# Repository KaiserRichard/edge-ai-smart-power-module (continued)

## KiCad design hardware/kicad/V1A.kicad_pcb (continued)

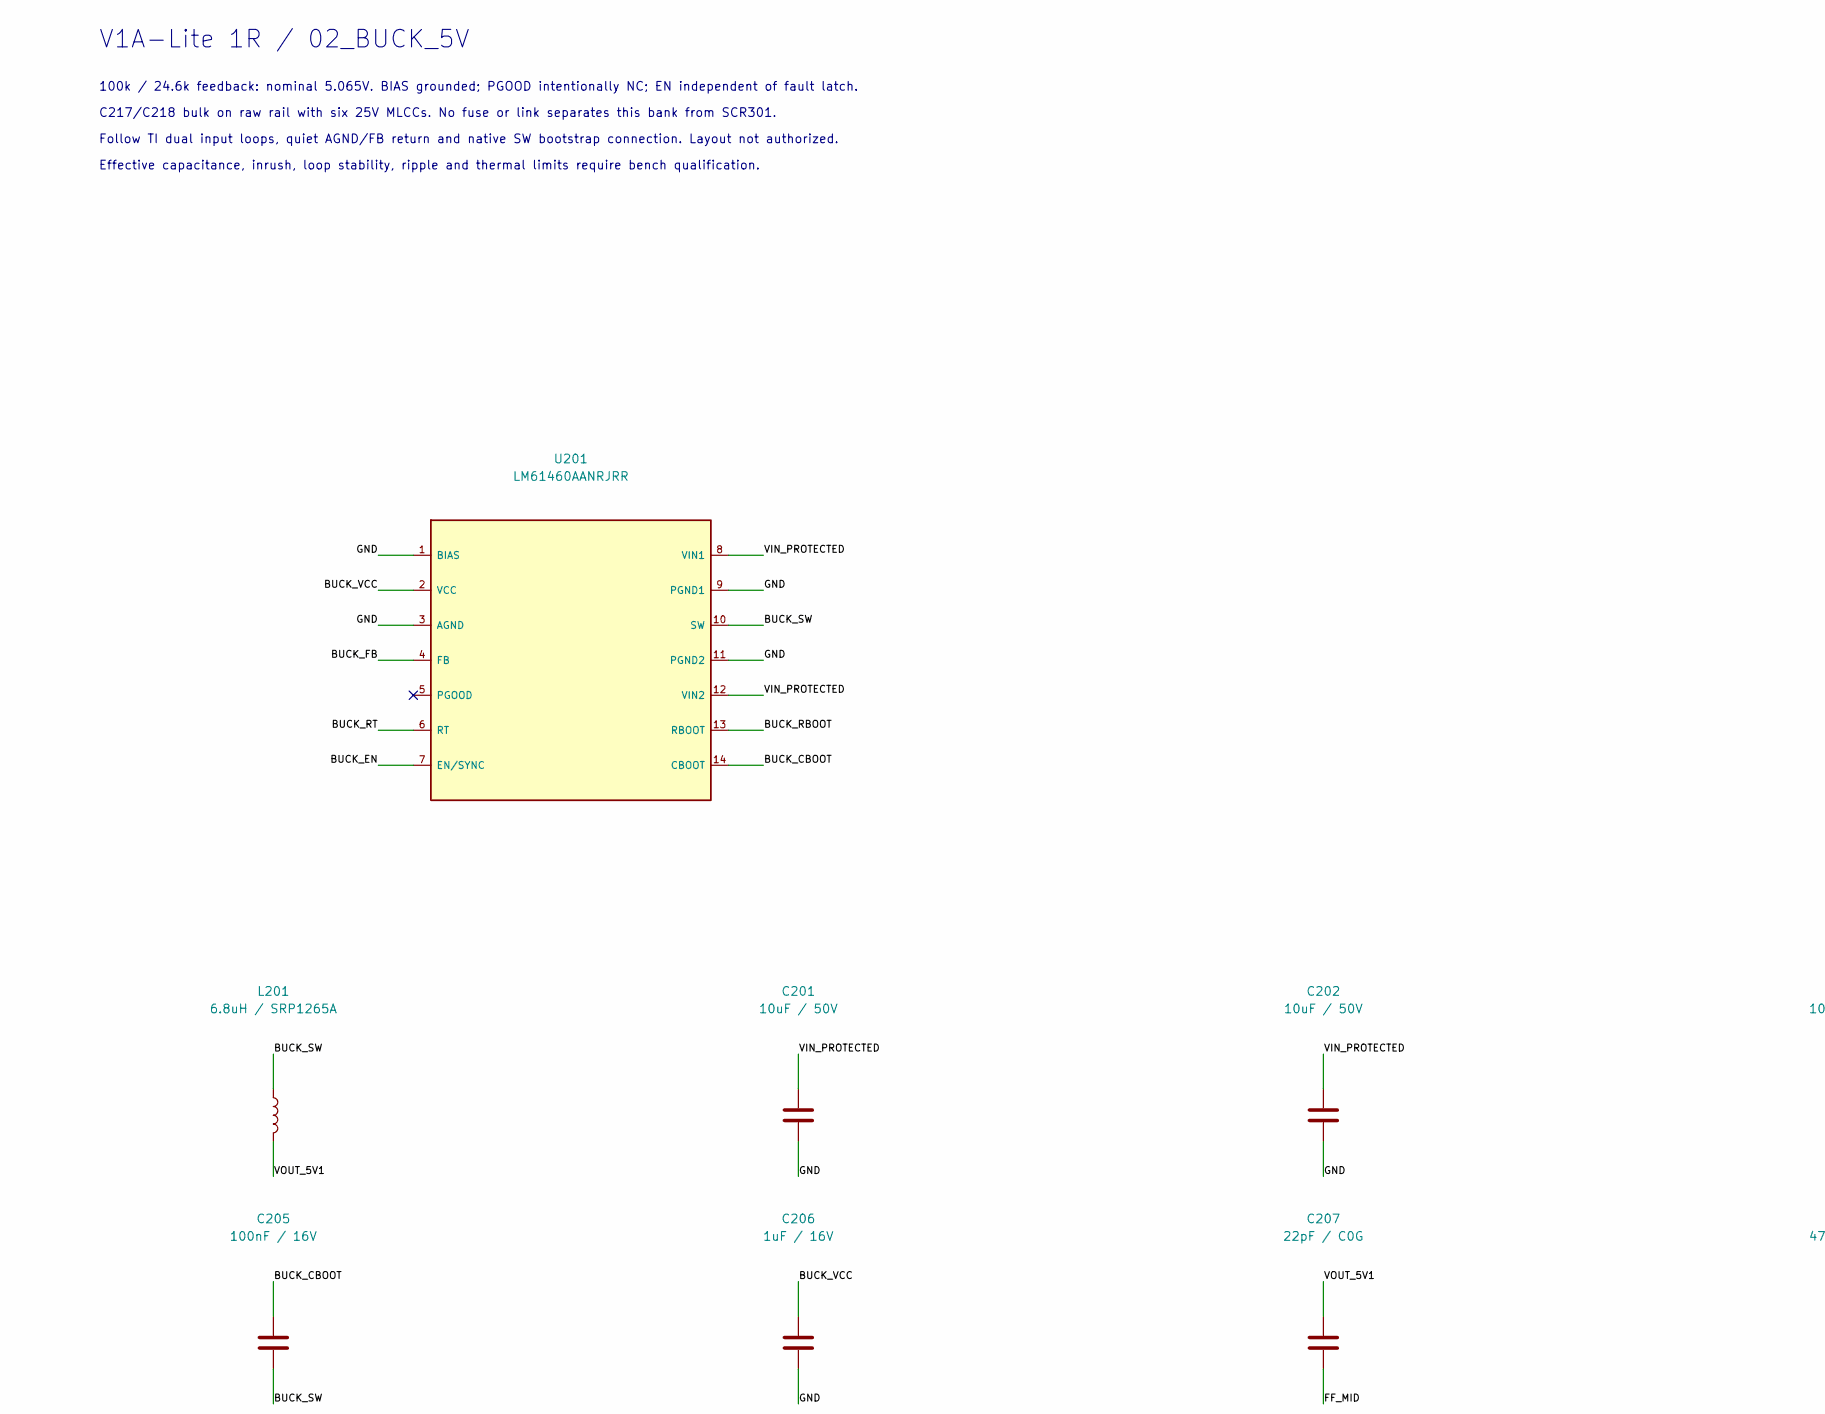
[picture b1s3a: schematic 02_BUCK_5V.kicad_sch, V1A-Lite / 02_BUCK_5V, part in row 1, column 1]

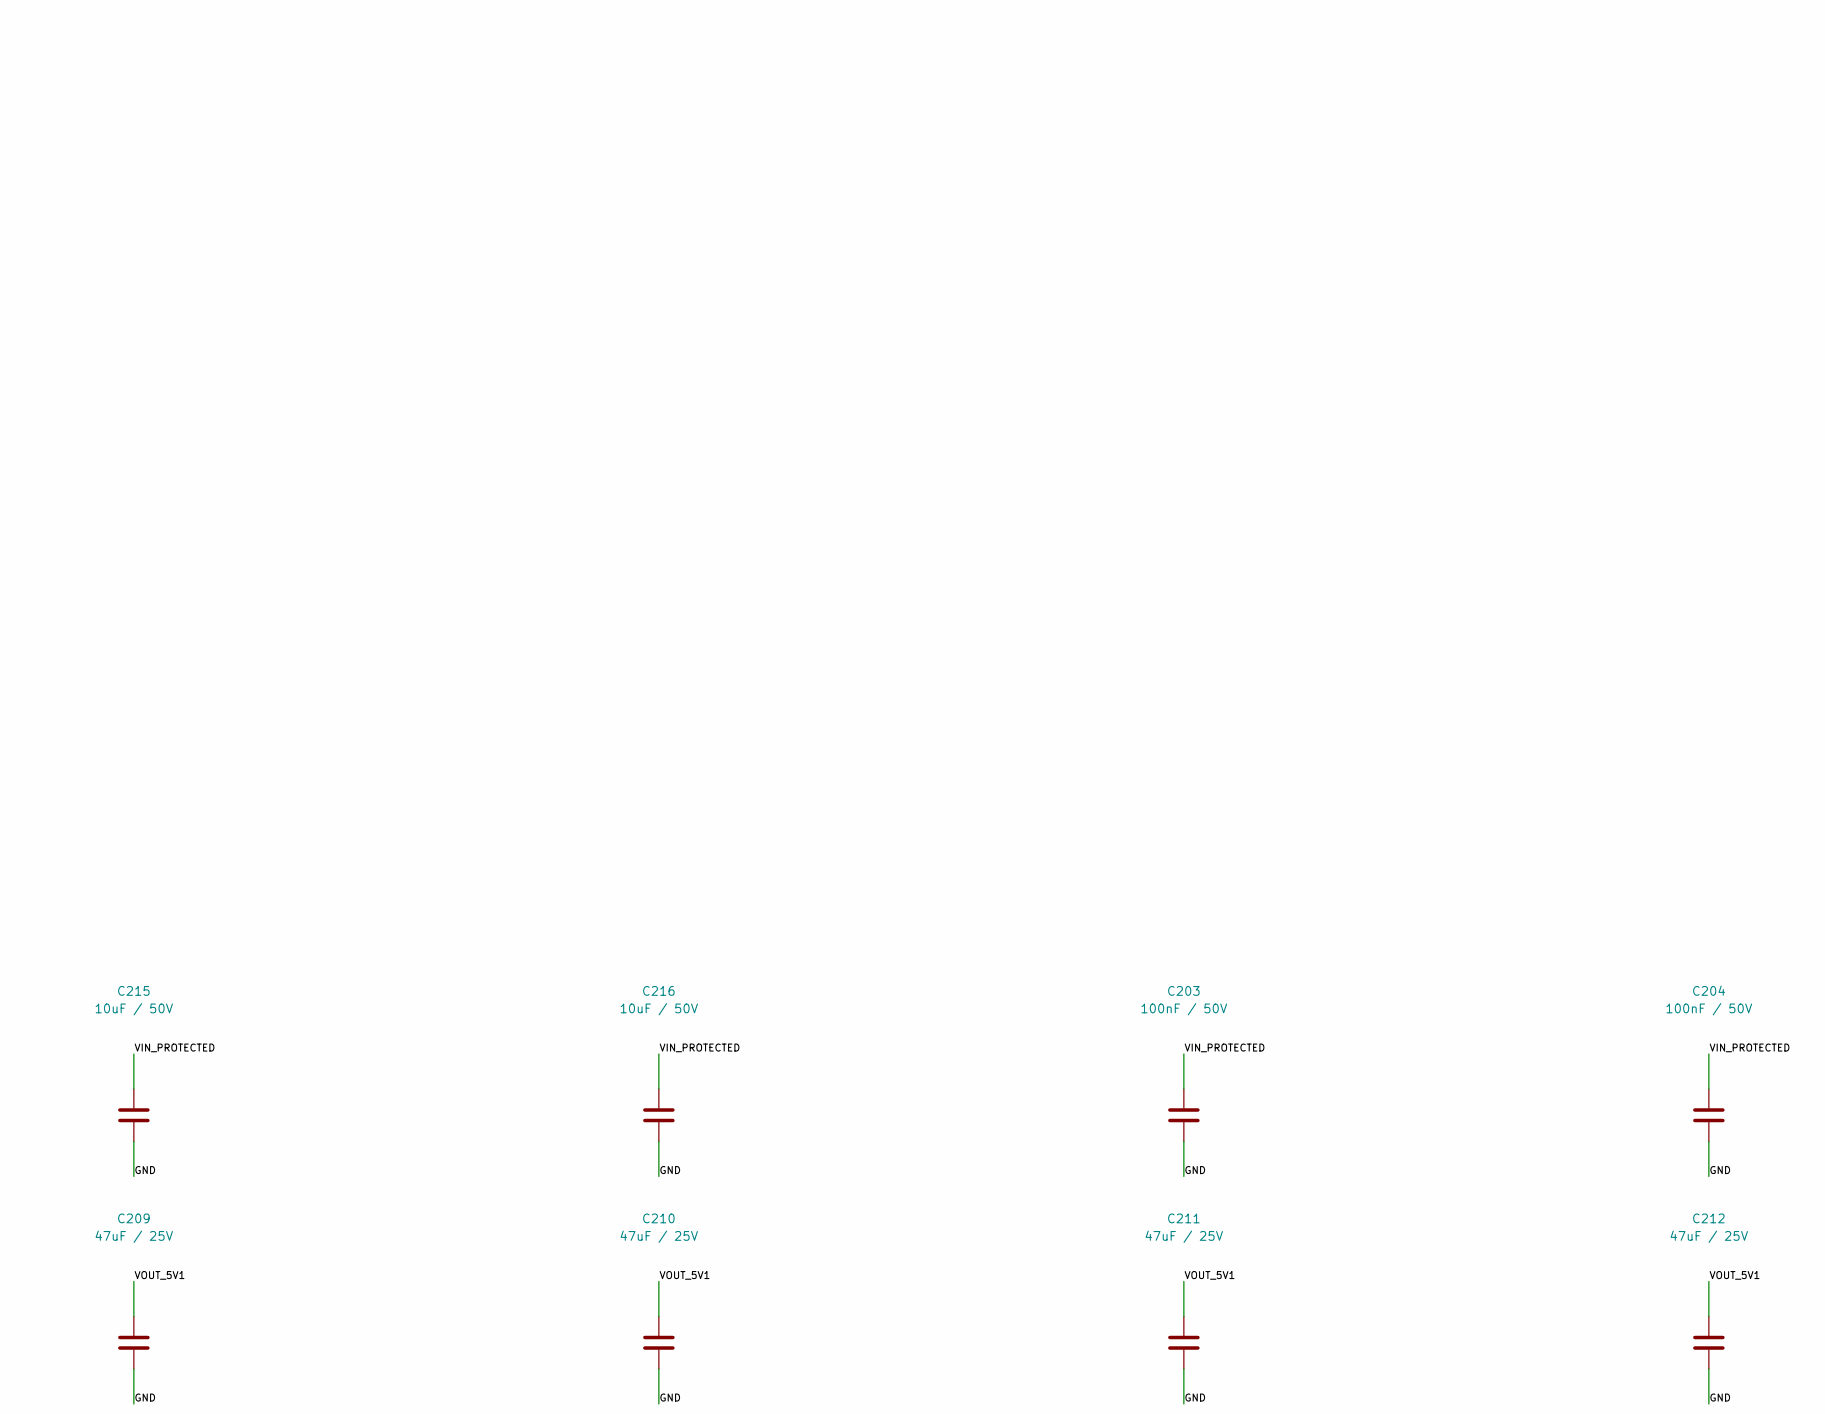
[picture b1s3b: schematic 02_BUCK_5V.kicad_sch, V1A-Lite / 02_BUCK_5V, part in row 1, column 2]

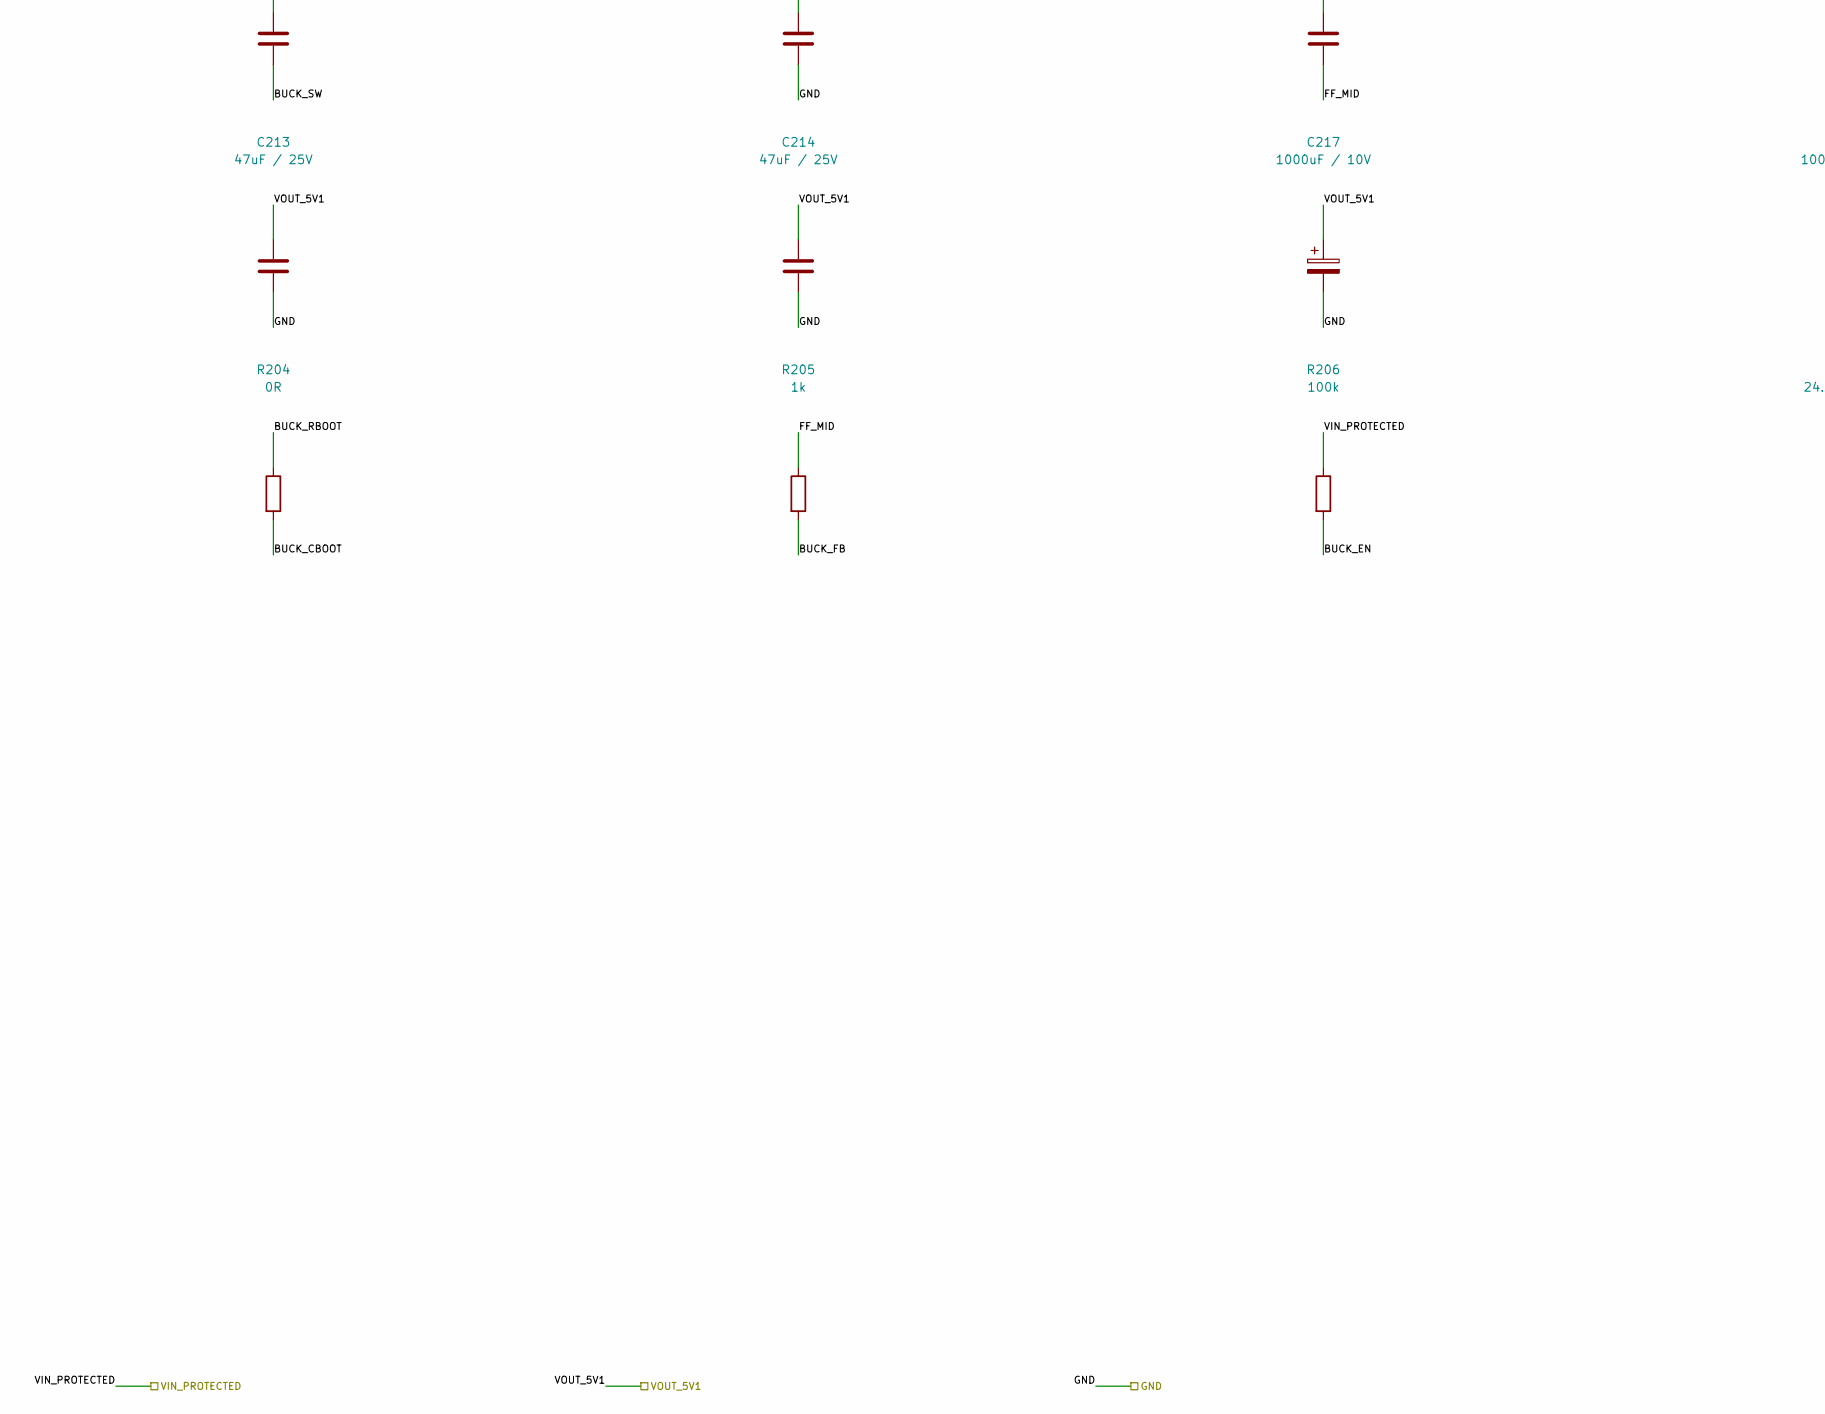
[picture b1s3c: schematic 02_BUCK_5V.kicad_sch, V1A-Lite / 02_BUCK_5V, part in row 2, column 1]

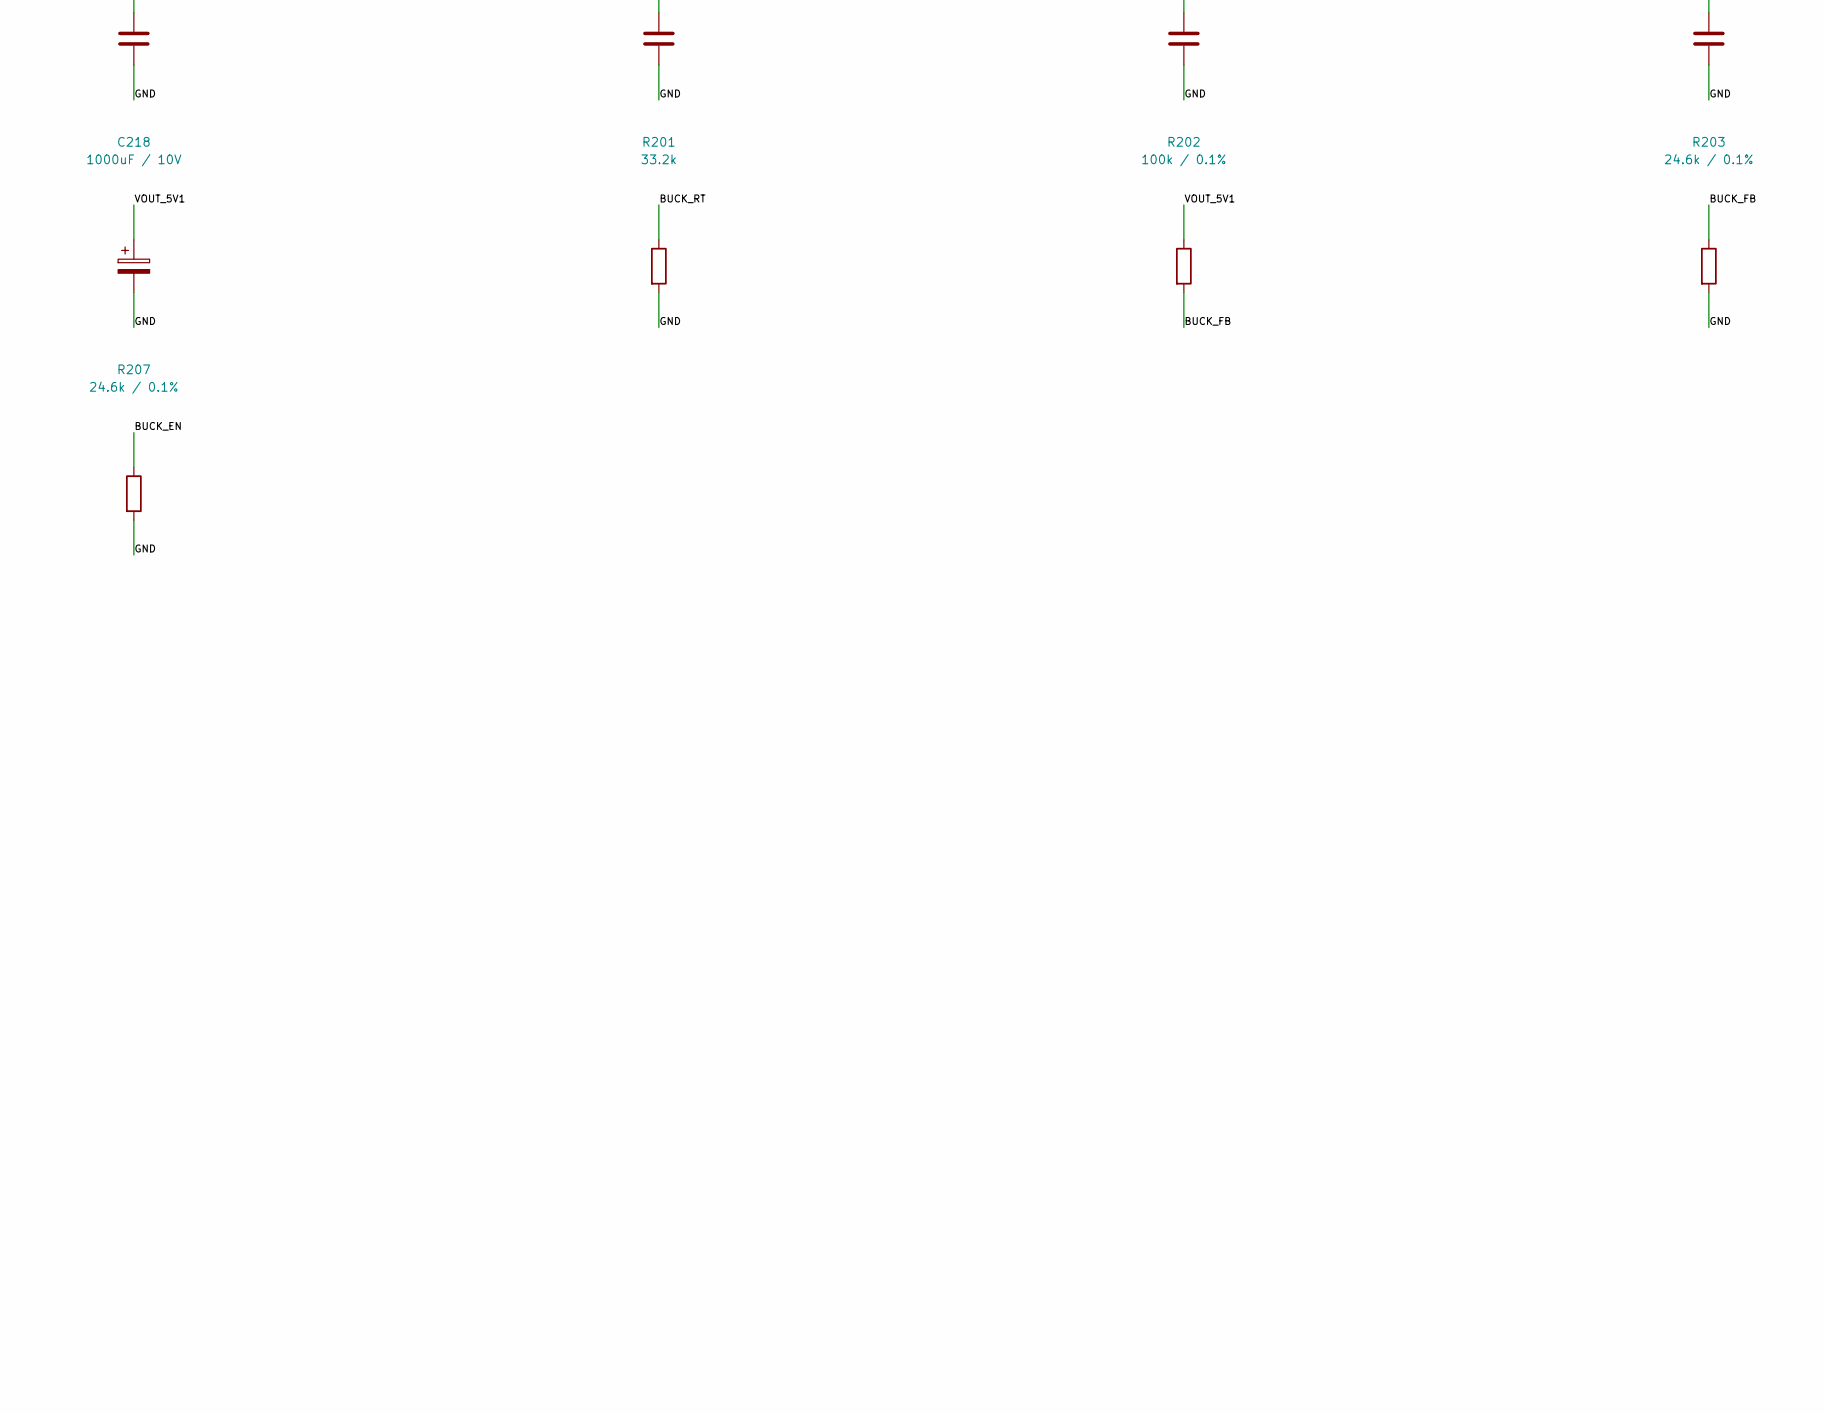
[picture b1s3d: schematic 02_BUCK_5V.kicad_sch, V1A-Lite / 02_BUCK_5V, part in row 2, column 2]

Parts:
C201, C202, C215, C216: 10uF / 50V; C_1210_3225Metric; MPN GRM32ER71H106KA12L; LCSC C77102
C203, C204: 100nF / 50V; C_0603_1608Metric; MPN GRM188R71H104KA93D; LCSC C77055
C205: 100nF / 16V; C_0603_1608Metric; MPN GRM188R71C104KA01D; LCSC C45000
C206: 1uF / 16V; C_0805_2012Metric; MPN GRM21BR71C105KA01L; LCSC C77079
C207: 22pF / C0G; C_0402_1005Metric; MPN C0402C220J4GACTU; LCSC C2168192
C209, C210, C211, C212, C213, C214: 47uF / 25V; C_1206_3216Metric; MPN GRM31CR61E476ME44L; LCSC C403725
C217, C218: 1000uF / 10V; CP_Radial_D10.0mm_P5.00mm; MPN EEUFR1A102; LCSC C407868
L201: 6.8uH / SRP1265A; Bourns_SRP1265A; MPN SRP1265A-6R8M; LCSC C2041326
R201: 33.2k; R_0603_1608Metric; MPN TNPW060333K2BEEA; LCSC C2075328
R202: 100k / 0.1%; R_0603_1608Metric; MPN TNPW0603100KBEEA; LCSC C844888
R203, R207: 24.6k / 0.1%; R_0603_1608Metric; MPN RT0603BRD0724K6L; LCSC C861250
R204: 0R; R_0603_1608Metric; MPN 0603WAF100JT5E; LCSC C22859
R205: 1k; R_0603_1608Metric; MPN 0603WAF1001T5E; LCSC C21190
R206: 100k; R_0603_1608Metric; MPN 0603WAF1003T5E; LCSC C25803
U201: LM61460AANRJRR; TI_RJR0014A_LM61460; MPN LM61460AANRJRR; LCSC C2864505

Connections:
/02_BUCK_5V/BUCK_CBOOT: C205.1, R204.2, U201.14 (CBOOT)
/02_BUCK_5V/BUCK_EN: R206.2, R207.1, U201.7 (EN/SYNC)
/02_BUCK_5V/BUCK_FB: R202.2, R203.1, R205.2, U201.4 (FB)
/02_BUCK_5V/BUCK_RBOOT: R204.1, U201.13 (RBOOT)
/02_BUCK_5V/BUCK_RT: R201.1, U201.6 (RT)
/02_BUCK_5V/BUCK_SW: C205.2, L201.1, U201.10 (SW)
/02_BUCK_5V/BUCK_VCC: C206.1, U201.2 (VCC)
/02_BUCK_5V/FF_MID: C207.2, R205.1
/GND: C201.2, C202.2, C203.2, C204.2, C206.2, C209.2, C210.2, C211.2, C212.2, C213.2, C214.2, C215.2, C216.2, C217.2, C218.2, R201.2, R203.2, R207.2, U201.1 (BIAS), U201.3 (AGND), U201.9 (PGND1), U201.11 (PGND2); also elsewhere on the board
/VIN_PROTECTED: C201.1, C202.1, C203.1, C204.1, C215.1, C216.1, R206.1, U201.8 (VIN1), U201.12 (VIN2); also elsewhere on the board
/VOUT_5V1: C207.1, C209.1, C210.1, C211.1, C212.1, C213.1, C214.1, C217.1, C218.1, L201.2, R202.1; also elsewhere on the board

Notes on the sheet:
V1A-Lite 1R / 02_BUCK_5V
100k / 24.6k feedback: nominal 5.065V. BIAS grounded; PGOOD intentionally NC; EN independent of fault latch.
C217/C218 bulk on raw rail with six 25V MLCCs. No fuse or link separates this bank from SCR301.
Follow TI dual input loops, quiet AGND/FB return and native SW bootstrap connection. Layout not authorized.
Effective capacitance, inrush, loop stability, ripple and thermal limits require bench qualification.

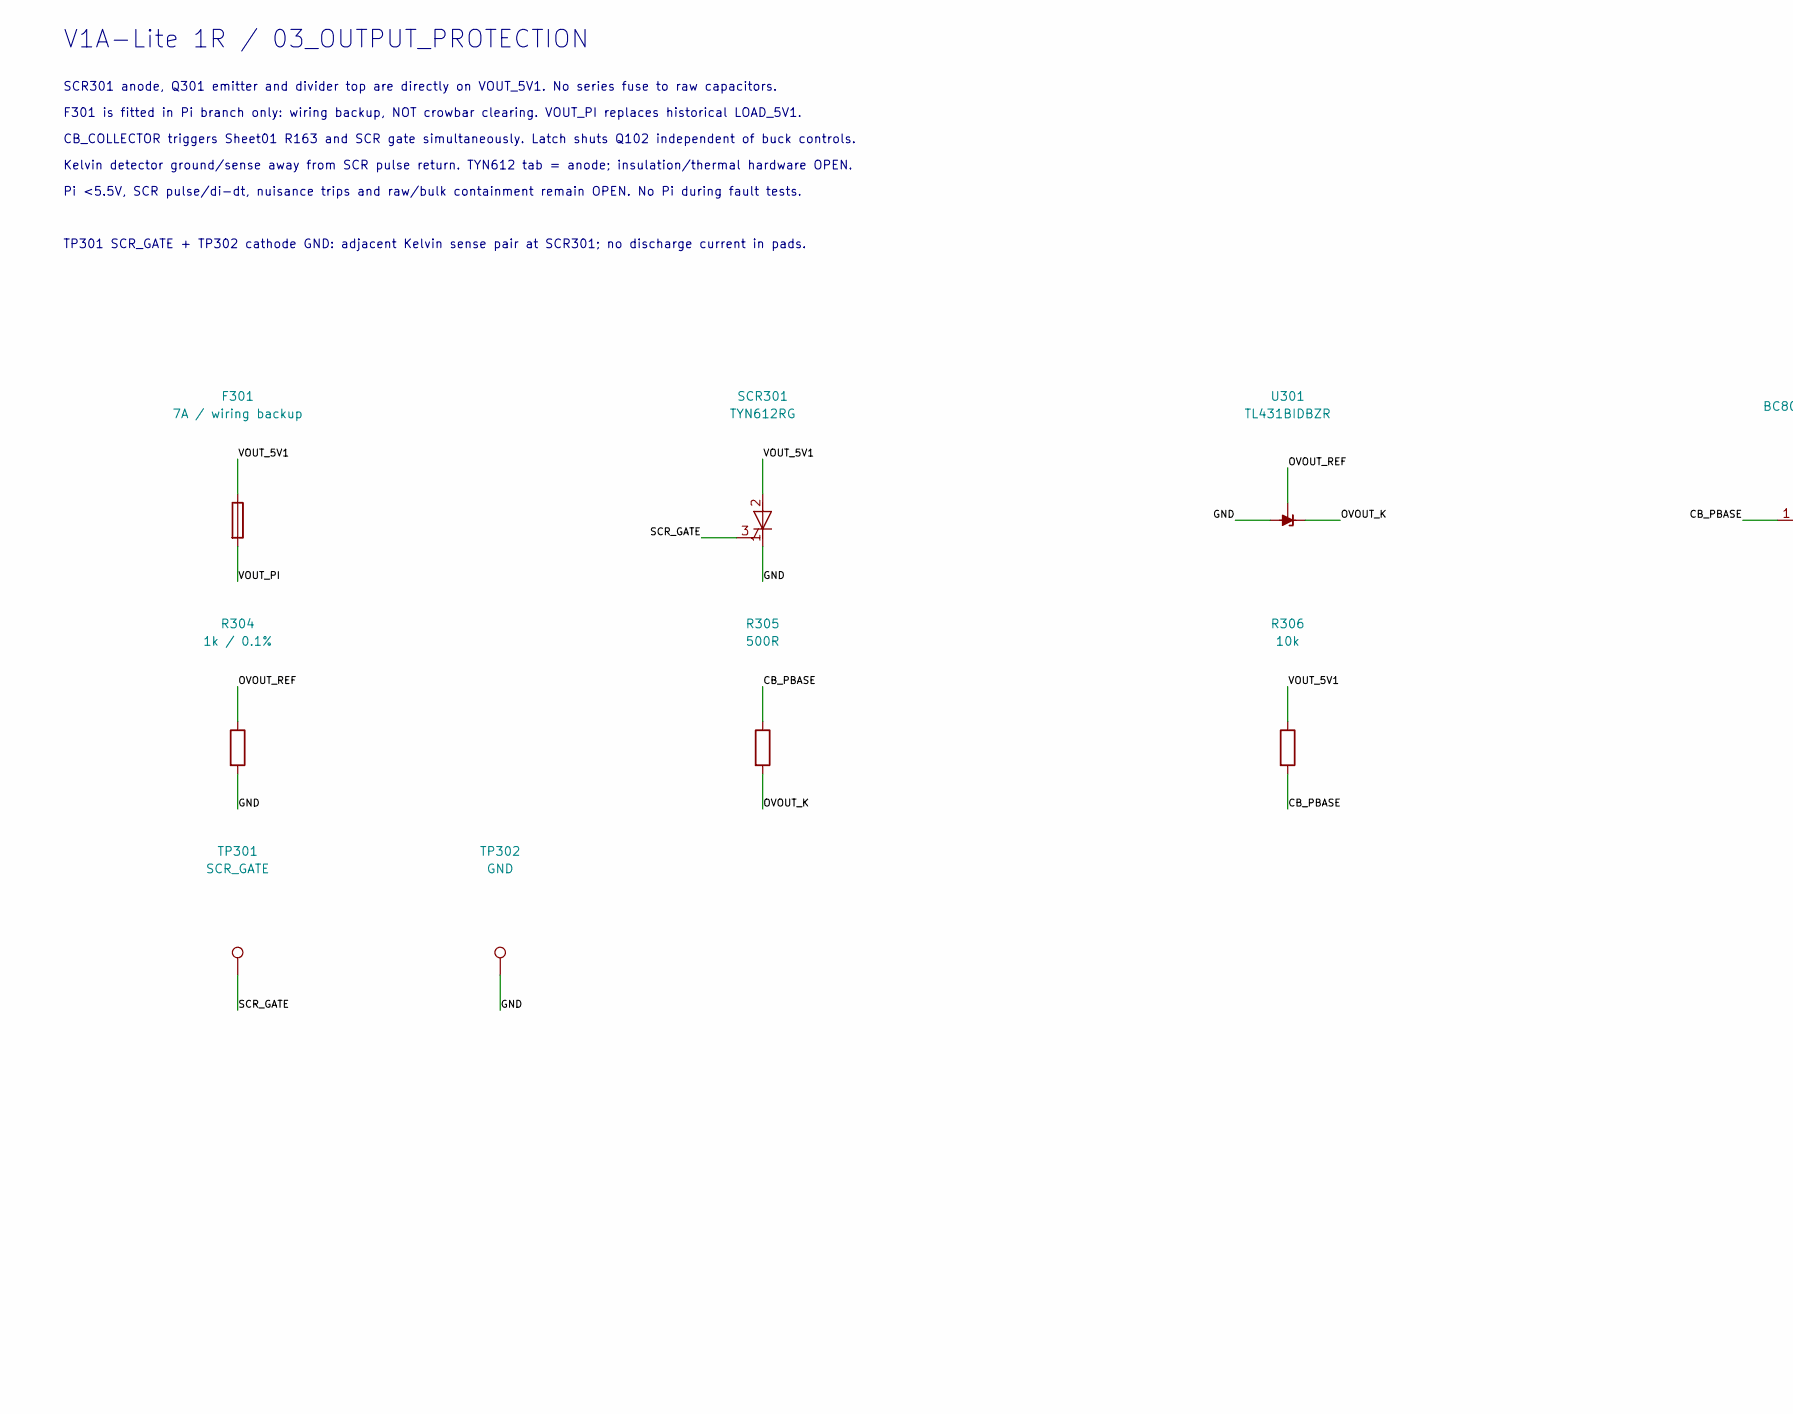
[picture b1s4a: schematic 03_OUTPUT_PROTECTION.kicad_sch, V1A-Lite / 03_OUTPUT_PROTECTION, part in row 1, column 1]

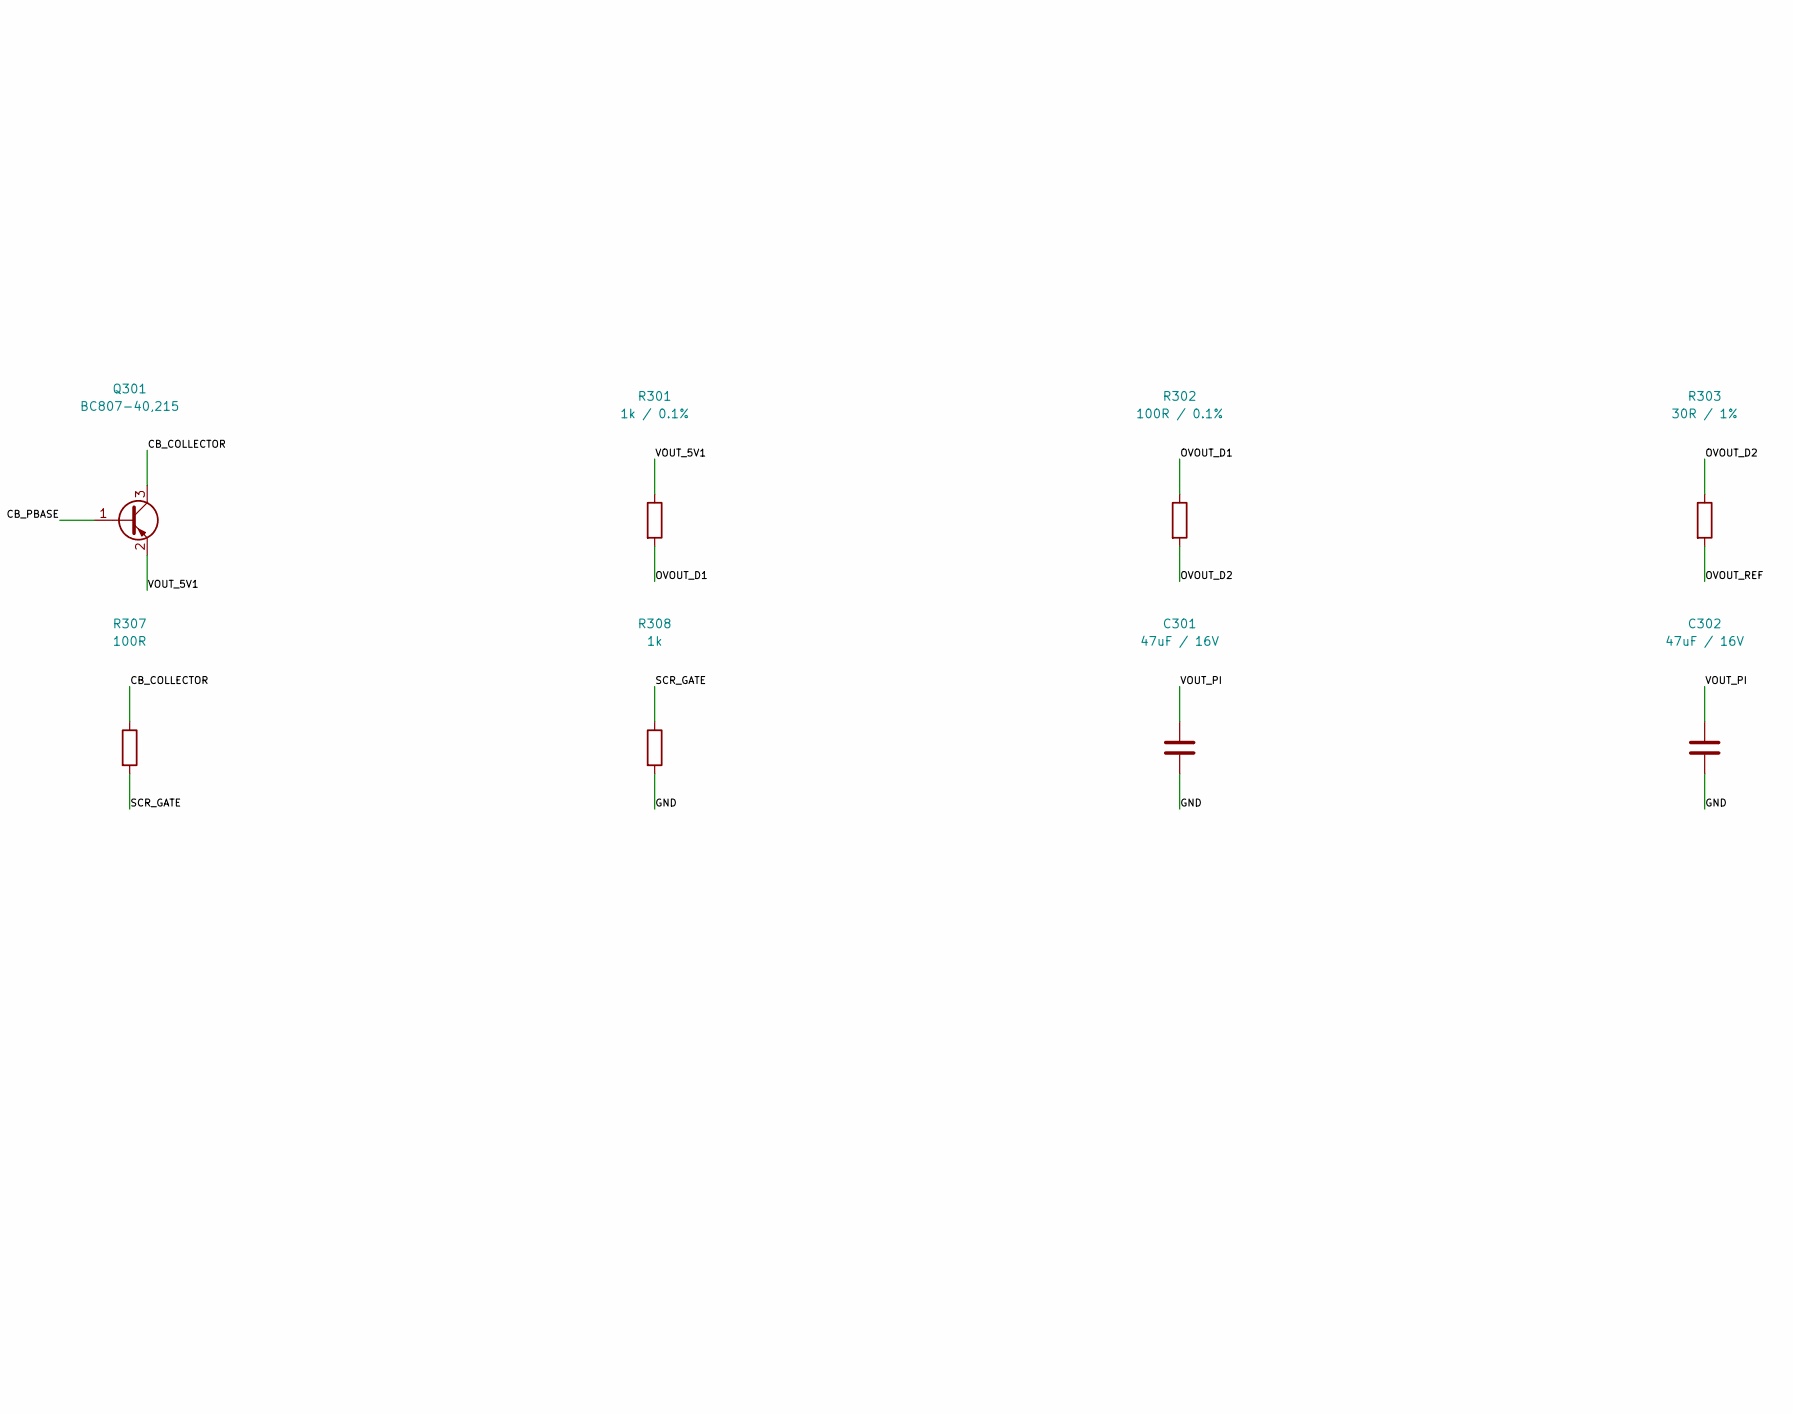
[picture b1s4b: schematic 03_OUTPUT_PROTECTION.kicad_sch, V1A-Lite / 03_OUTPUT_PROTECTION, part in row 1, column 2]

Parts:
C301, C302: 47uF / 16V; C_1210_3225Metric; MPN GRM32ER61C476KE15L; LCSC C77101
F301: 7A / wiring backup; Fuse_Littelfuse-NANO2-451_453; MPN 0451007.MRL; LCSC C99548
Q301: BC807-40,215; SOT-23; MPN BC807-40,215; LCSC C57316
R301, R304: 1k / 0.1%; R_0603_1608Metric; MPN RT0603BRD071KL; LCSC C110776
R302: 100R / 0.1%; R_0603_1608Metric; MPN TNPW0603100RBEEA; LCSC C844889
R303: 30R / 1%; R_0603_1608Metric; MPN 0603WAF1300T5E; LCSC C22796
R305: 500R; R_0603_1608Metric; MPN 0603WAF1501T5E; LCSC C22843
R306: 10k; R_0805_2012Metric; MPN 0805W8F1002T5E; LCSC C17414
R307: 100R; R_0603_1608Metric; MPN 0603WAF1000T5E; LCSC C22775
R308: 1k; R_0603_1608Metric; MPN 0603WAF1001T5E; LCSC C21190
SCR301: TYN612RG; TO-220-3_Vertical; MPN TYN612RG; LCSC C262993
TP301: SCR_GATE; TestPoint_Pad_D2.0mm; MPN PCB_FEATURE; LCSC N/A
TP302: GND; TestPoint_Pad_D2.0mm; MPN PCB_FEATURE; LCSC N/A
U301: TL431BIDBZR; SOT-23; MPN TL431BIDBZR; LCSC C41283

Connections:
/03_OUTPUT_PROTECTION/CB_PBASE: Q301.1 (B), R305.1, R306.2
/03_OUTPUT_PROTECTION/OVOUT_D1: R301.2, R302.1
/03_OUTPUT_PROTECTION/OVOUT_D2: R302.2, R303.1
/03_OUTPUT_PROTECTION/OVOUT_K: R305.2, U301.1 (K)
/03_OUTPUT_PROTECTION/OVOUT_REF: R303.2, R304.1, U301.2 (REF)
/03_OUTPUT_PROTECTION/SCR_GATE: R307.2, R308.1, SCR301.3 (G), TP301.1
/CB_COLLECTOR: Q301.3 (C), R307.1; also elsewhere on the board
/GND: C301.2, C302.2, R304.2, R308.2, SCR301.1 (K), TP302.1, U301.3 (A); also elsewhere on the board
/VOUT_5V1: F301.1, Q301.2 (E), R301.1, R306.1, SCR301.2 (A); also elsewhere on the board
/VOUT_PI: C301.1, C302.1, F301.2; also elsewhere on the board

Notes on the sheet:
V1A-Lite 1R / 03_OUTPUT_PROTECTION
SCR301 anode, Q301 emitter and divider top are directly on VOUT_5V1. No series fuse to raw capacitors.
F301 is fitted in Pi branch only: wiring backup, NOT crowbar clearing. VOUT_PI replaces historical LOAD_5V1.
CB_COLLECTOR triggers Sheet01 R163 and SCR gate simultaneously. Latch shuts Q102 independent of buck controls.
Kelvin detector ground/sense away from SCR pulse return. TYN612 tab = anode; insulation/thermal hardware OPEN.
Pi <5.5V, SCR pulse/di-dt, nuisance trips and raw/bulk containment remain OPEN. No Pi during fault tests.
TP301 SCR_GATE + TP302 cathode GND: adjacent Kelvin sense pair at SCR301; no discharge current in pads.
